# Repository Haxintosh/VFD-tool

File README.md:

# VFD-tool
A modular multitool designed for engineers with a VFD screen (WIP!!!!!!!)

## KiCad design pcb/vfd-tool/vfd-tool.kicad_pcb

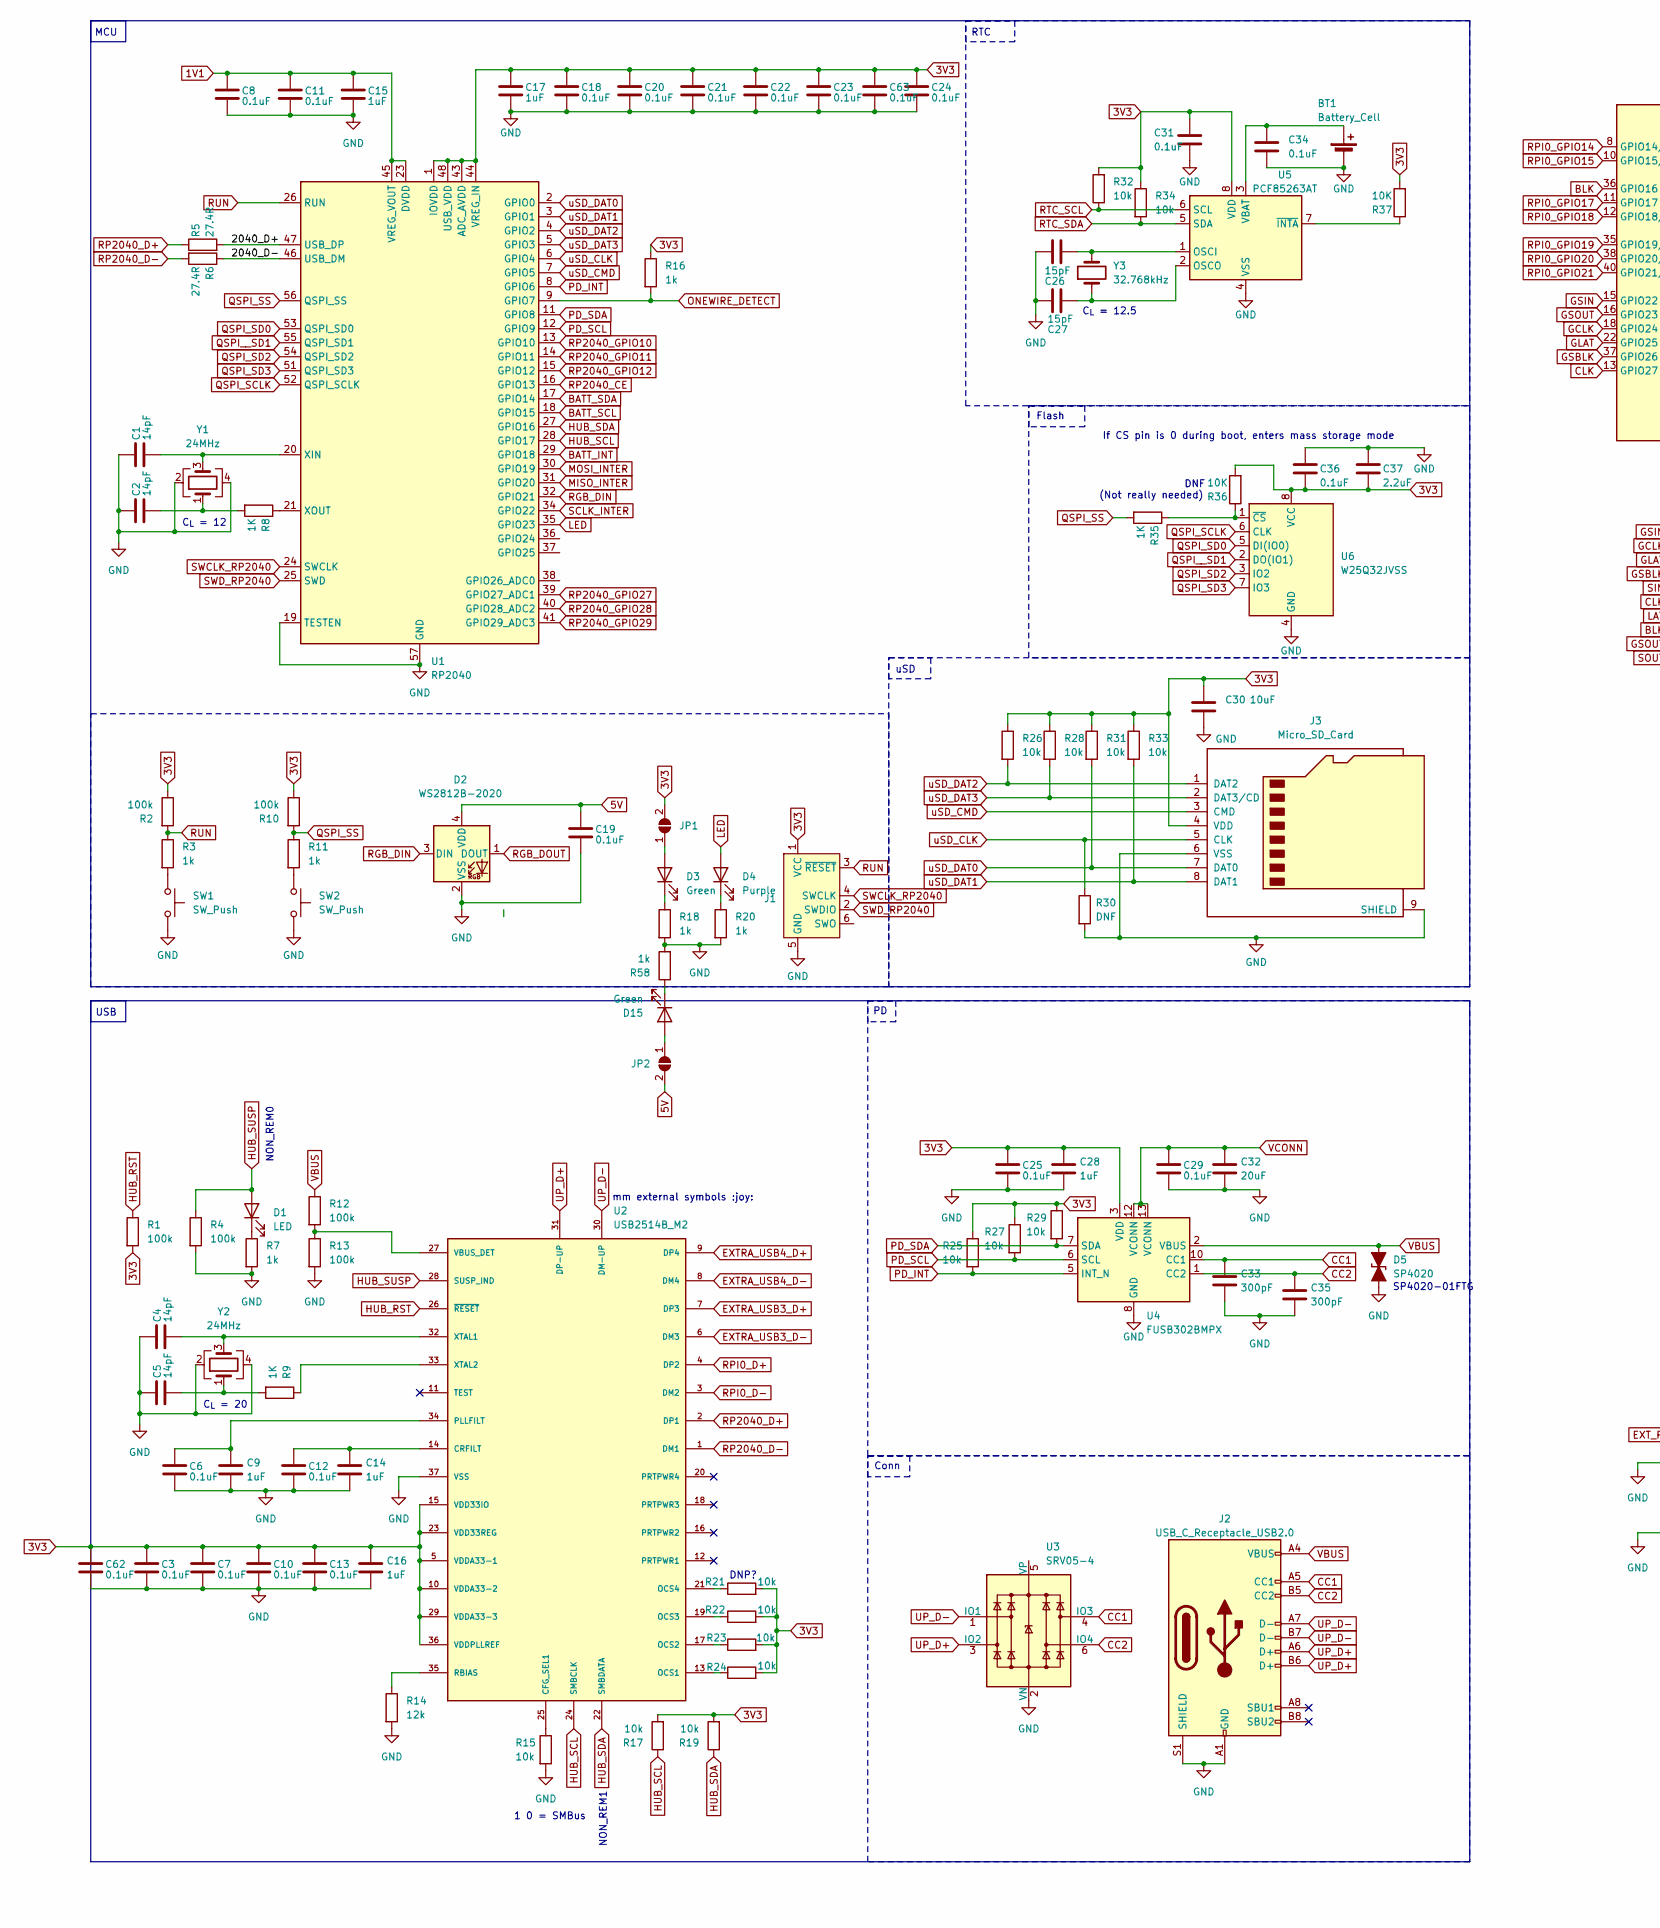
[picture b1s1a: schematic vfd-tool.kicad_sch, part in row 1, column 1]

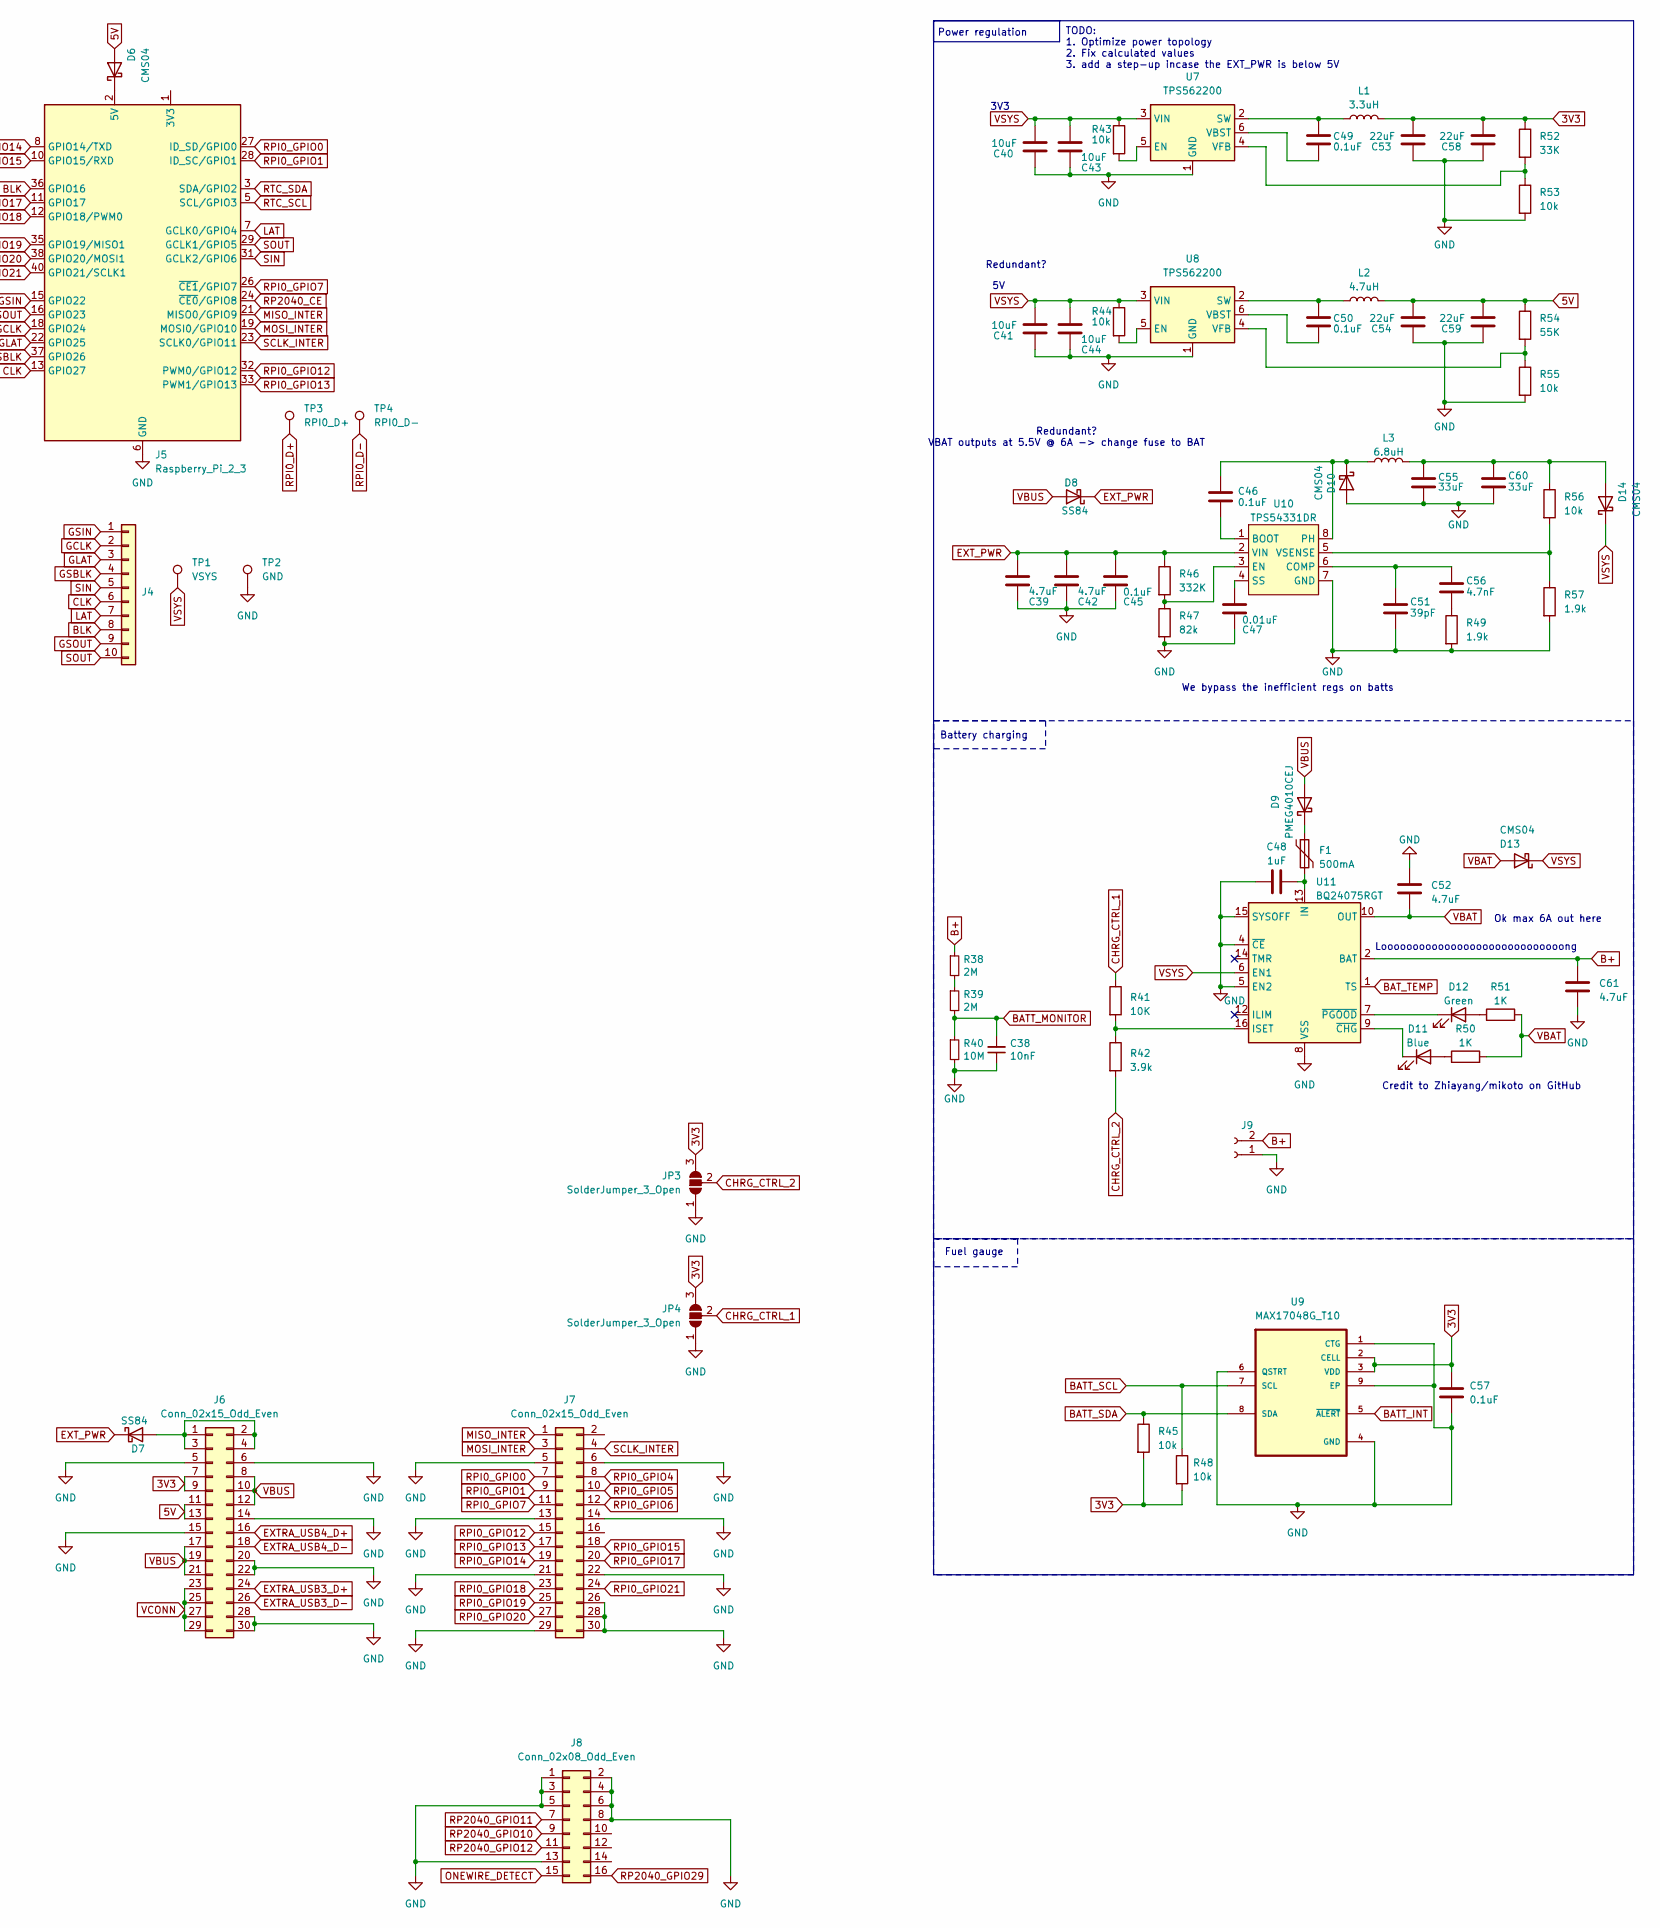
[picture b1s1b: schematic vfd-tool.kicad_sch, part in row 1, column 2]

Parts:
BT1: Battery_Cell; BAT_CR2032-BS-6-1
C1, C2, C4, C5: 14pF; C_0402_1005Metric_Pad0.74x0.62mm_HandSolder
C3, C6, C7, C8, C10, C11, C12, C13, C18, C19, C20, C21, C22, C23, C24, C25, C29, C36, C46, C49, C50, C57, C62, C63: 0.1uF; C_0402_1005Metric_Pad0.74x0.62mm_HandSolder
C9, C14, C15, C17: 1uF; C_0402_1005Metric_Pad0.74x0.62mm_HandSolder
C16: 1uF; R_0402_1005Metric
C26, C27: 15pF; C_0402_1005Metric_Pad0.74x0.62mm_HandSolder
C28: 1uF; C_0603_1608Metric
C30, C40, C41, C43, C44: 10uF; C_0603_1608Metric
C31, C34: 0.1uF; C_0402_1005Metric
C32: 20uF; C_0805_2012Metric
C33, C35: 300pF; C_0402_1005Metric
C37: 2.2uF; C_0603_1608Metric
C38: 10nF; C_0402_1005Metric_Pad0.74x0.62mm_HandSolder; Manufacturer Part CL05B103KB5NNNC; LCSC Part C15195
C39, C42: 4.7uF; C_0805_2012Metric
C45: 0.1uF; C_0603_1608Metric
C47: 0.01uF; C_0402_1005Metric_Pad0.74x0.62mm_HandSolder
C48: 1uF; C_0603_1608Metric_Pad1.08x0.95mm_HandSolder
C51: 39pF; C_0402_1005Metric_Pad0.74x0.62mm_HandSolder
C52, C61: 4.7uF; C_0603_1608Metric_Pad1.08x0.95mm_HandSolder
C53, C54, C58, C59: 22uF; C_0603_1608Metric
C55, C60: 33uF; C_0805_2012Metric
C56: 4.7nF; C_0402_1005Metric_Pad0.74x0.62mm_HandSolder
D1: LED; LED_0603_1608Metric
D2: WS2812B-2020; LED_WS2812B-2020_PLCC4_2.0x2.0mm
D3, D15: Green; LED_0603_1608Metric
D4: Purple; LED_0603_1608Metric
D5: SP4020; D_SOD-323
D6, D10, D13, D14: CMS04; D_SOD-128
D7, D8: SS84; D_SMC
D9: PMEG4010CEJ; D_SOD-323_HandSoldering
D11: Blue; LED_0603_1608Metric_Pad1.05x0.95mm_HandSolder
D12: Green; LED_0603_1608Metric_Pad1.05x0.95mm_HandSolder
F1: 500mA; Fuse_0402_1005Metric_Pad0.77x0.64mm_HandSolder
J1: Conn_ARM_SWD_TagConnect_TC2030-NL; Paw-Connect_RevA_TC2030-IDC-NL_2x03_P1.27mm_Vertical
J2: USB_C_Receptacle_USB2.0; USB_C_Receptacle_G-Switch_GT-USB-7010ASV
J3: Micro_SD_Card; TF-01A
J4: Conn_01x10; MOLEX_5034801000
J5: Raspberry_Pi_2_3; MODULE_ADA3708
J6, J7: Conn_02x15_Odd_Even; PinHeader_2x15_P1.27mm_Vertical
J8: Conn_02x08_Odd_Even; PinHeader_2x08_P1.27mm_Vertical
J9: Conn_01x02_Socket; JST_PH_B2B-PH-SM4-TB_1x02-1MP_P2.00mm_Vertical
JP1, JP2: SolderJumper_2_Open; SolderJumper-2_P1.3mm_Open_TrianglePad1.0x1.5mm
JP3, JP4: SolderJumper_3_Open; SolderJumper-3_P2.0mm_Open_TrianglePad1.0x1.5mm
L1: 3.3uH; L_Chilisin_BMRB00060612
L2: 4.7uH; L_Chilisin_BMRB00060612
L3: 6.8uH; L_Chilisin_BMRB00060612
R1, R2, R4, R10, R12, R13: 100k; R_0402_1005Metric_Pad0.72x0.64mm_HandSolder
R3, R7, R11: 1k; R_0402_1005Metric_Pad0.72x0.64mm_HandSolder
R5, R6: 27.4R; R_0402_1005Metric_Pad0.72x0.64mm_HandSolder
R8, R9, R35, R50, R51: 1K; R_0402_1005Metric_Pad0.72x0.64mm_HandSolder
R14: 12k; R_0402_1005Metric_Pad0.72x0.64mm_HandSolder
R15, R17, R19, R21, R22, R23, R24, R25, R26, R27, R28, R29, R31, R32, R33, R34, R43, R44, R53, R55: 10k; R_0402_1005Metric_Pad0.72x0.64mm_HandSolder
R16, R18, R20, R58: 1k; R_0402_1005Metric
R30: DNF; R_0402_1005Metric_Pad0.72x0.64mm_HandSolder
R36, R37, R41: 10K; R_0402_1005Metric_Pad0.72x0.64mm_HandSolder
R38, R39: 2M; R_0402_1005Metric_Pad0.72x0.64mm_HandSolder; Manufacturer Part RC0402FR-072ML; LCSC Part C138014
R40: 10M; R_0402_1005Metric_Pad0.72x0.64mm_HandSolder; Manufacturer Part RC0402FR-0710ML; LCSC Part C138067
R42: 3.9k; R_0402_1005Metric_Pad0.72x0.64mm_HandSolder
R45, R48: 10k; R_0603_1608Metric
R46: 332K; R_0402_1005Metric
R47: 82k; R_0402_1005Metric
R49, R57: 1.9k; R_0402_1005Metric
R52: 33K; R_0402_1005Metric_Pad0.72x0.64mm_HandSolder
R54: 55K; R_0402_1005Metric_Pad0.72x0.64mm_HandSolder
R56: 10k; R_0402_1005Metric
SW1, SW2: SW_Push; SW_SPST_B3U-1000P
TP1: VSYS; TestPoint_Pad_D3.0mm
TP2: GND; TestPoint_Pad_D3.0mm
TP3: RPI0_D+; TestPoint_Pad_D1.0mm
TP4: RPI0_D-; TestPoint_Pad_D1.0mm
U1: RP2040; QFN-56-1EP_7x7mm_P0.4mm_EP3.2x3.2mm
U2: USB2514B_M2; 36-SQFN-EXPOSED-PAD
U3: SRV05-4; SOT-23-6
U4: FUSB302BMPX; WQFN-14-1EP_2.5x2.5mm_P0.5mm_EP1.45x1.45mm
U5: PCF85263AT; SOIC-8_3.9x4.9mm_P1.27mm
U6: W25Q32JVSS; SOIC-8_5.23x5.23mm_P1.27mm
U7, U8: TPS562200; SOT-23-6
U9: MAX17048G_T10; DFN-8-1EP_2x2mm_P0.5mm_EP0.6x1.2mm
U10: TPS54331DR; SOIC-8_3.9x4.9mm_P1.27mm
U11: BQ24075RGT; VQFN-16-1EP_3x3mm_P0.5mm_EP1.6x1.6mm
Y1, Y2: 24MHz; Crystal_SMD_3225-4Pin_3.2x2.5mm; LCSC C133334
Y3: 32.768kHz; Crystal_SMD_3215-2Pin_3.2x1.5mm

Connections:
1V1: C8.1, C11.1, C15.1, U1.23 (DVDD), U1.45 (VREG_VOUT), U1.50 (DVDD)
3V3: C3.1, C7.1, C10.1, C13.1, C16.1, C17.1, C18.1, C20.1, C21.1, C22.1, C23.1, C24.1, C25.1, C28.1, C30.1, C31.1, C36.2, C37.2, C53.2, C57.1, C58.2, C62.1, C63.1, J1.1 (VCC), J3.4 (VDD), J6.7, J6.9, JP1.2 (B), JP3.3 (B), JP4.3 (B), L1.2, R1.2, R2.1, R10.1, R16.1, R17.2, R19.2, R21.2, R22.2, R23.2, R24.2, R25.1, R26.1, R27.1, R28.1, R29.1, R31.1, R32.2, R33.1, R34.1, R36.2, R37.2, R45.2, R48.2, R52.1, U1.1 (IOVDD), U1.10 (IOVDD), U1.22 (IOVDD), U1.33 (IOVDD), U1.42 (IOVDD), U1.43 (ADC_AVDD), U1.44 (VREG_IN), U1.48 (USB_VDD), U1.49 (IOVDD), U2.5 (VDDA33-1), U2.10 (VDDA33-2), U2.15 (VDD33IO), U2.23 (VDD33REG), U2.29 (VDDA33-3), U2.36 (VDDPLLREF), U4.3 (VDD), U4.4 (VDD), U5.8 (VDD), U6.8 (VCC), U9.2 (CELL), U9.3 (VDD)
5V: C19.1, C54.2, C59.2, D2.4 (VDD), D6.2 (A), J6.11, J6.13, JP2.2 (B), L2.2, R54.1
/2040_D+: R5.2, U1.47 (USB_DP)
/2040_D-: R6.1, U1.46 (USB_DM)
B+: C61.2, J9.2, R38.1, U11.2 (BAT), U11.3 (BAT)
BATT_INT: U1.29 (GPIO18), U9.5 (~ALERT)
BATT_MONITOR: C38.2, R39.2, R40.1
BATT_SCL: R48.1, U1.18 (GPIO15), U9.7 (SCL)
BATT_SDA: R45.1, U1.17 (GPIO14), U9.8 (SDA)
BAT_TEMP: U11.1 (TS)
BLK: J4.8, J5.36 (GPIO16)
CC1: C33.1, J2.A5 (CC1), U3.4 (IO3), U4.10 (CC1), U4.11 (CC1)
CC2: C35.1, J2.B5 (CC2), U3.6 (IO4), U4.1 (CC2), U4.14 (CC2)
CHRG_CTRL_1: JP4.2 (C), R41.1
CHRG_CTRL_2: JP3.2 (C), R42.2
CLK: J4.6, J5.13 (GPIO27)
EXTRA_USB3_D+: J6.24, U2.7 (DP3)
EXTRA_USB3_D-: J6.26, U2.6 (DM3)
EXTRA_USB4_D+: J6.16, U2.9 (DP4)
EXTRA_USB4_D-: J6.18, U2.8 (DM4)
EXT_PWR: C39.1, C42.1, C45.1, D7.1 (K), D8.1 (K), R46.1, U10.2 (VIN)
GCLK: J4.2, J5.18 (GPIO24)
GLAT: J4.3, J5.22 (GPIO25)
GND: BT1.N (-), C1.1, C2.1, C3.2, C4.1, C5.1, C6.2, C7.2, C8.2, C9.2, C10.2, C11.2, C12.2, C13.2, C14.2, C15.2, C16.2, C17.2, C18.2, C19.2, C20.2, C21.2, C22.2, C23.2, C24.2, C25.2, C26.2, C27.2, C28.2, C29.2, C30.2, C31.2, C32.2, C33.2, C34.2, C35.2, C36.1, C37.1, C38.1, C39.2, C40.1, C41.1, C42.2, C43.2, C44.2, C45.2, C47.2, C48.2, C51.2, C52.1, C53.1, C54.1, C55.2, C57.2, C58.1, C59.1, C60.2, C61.1, C62.2, C63.2, D2.2 (VSS), D5.2 (A2), D10.2 (A), J1.5 (GND), J2.A1 (GND), J2.A12 (GND), J2.B1 (GND), J2.B12 (GND), J2.S1 (SHIELD), J3.6 (VSS), J3.9 (SHIELD), J5.6 (GND), J5.9 (GND), J5.14 (GND), J5.20 (GND), J5.25 (GND), J5.30 (GND), J5.34 (GND), J5.39 (GND), J6.5, J6.6, J6.14, J6.15, J6.20, J6.22, J6.28, J6.30, J7.5, J7.6, J7.13, J7.14, J7.21, J7.22, J7.26, J7.28, J7.29, J7.30, J8.1, J8.2, J8.3, J8.4, J8.5, J8.6, J8.8, J8.13, J9.1, JP3.1 (A), JP4.1 (A), R4.2, R7.2, R13.2, R14.2, R15.2, R18.2, R20.2, R30.2, R40.2, R47.2, R49.2, R53.2, R55.2, R57.2, R58.2, SW1.2, SW2.2, TP2.1, U1.19 (TESTEN), U1.57 (GND), U2.37 (VSS), U3.2 (VN), U4.8 (GND), U4.9 (GND), U4.15 (GND), U5.4 (VSS), U6.4 (GND), U7.1 (GND), U8.1 (GND), U9.1 (CTG), U9.4 (GND), U9.6 (QSTRT), U9.9 (EP), U10.7 (GND), U11.4 (~CE), U11.5 (EN2), U11.8 (VSS), U11.15 (SYSOFF), U11.17 (VSS), Y1.2, Y1.4, Y2.2, Y2.4
GSBLK: J4.4, J5.37 (GPIO26)
GSIN: J4.1, J5.15 (GPIO22)
GSOUT: J4.9, J5.16 (GPIO23)
HUB_RST: R1.1, U2.26 (~RESET)
HUB_SCL: R17.1, U1.28 (GPIO17), U2.24 (SMBCLK)
HUB_SDA: R19.1, U1.27 (GPIO16), U2.22 (SMBDATA)
HUB_SUSP: D1.2 (A), R4.1, U2.28 (SUSP_IND)
LAT: J4.7, J5.7 (GCLK0/GPIO4)
LED: D4.2 (A), U1.35 (GPIO23)
MISO_INTER: J5.21 (MISO0/GPIO9), J7.1, U1.31 (GPIO20)
MOSI_INTER: J5.19 (MOSI0/GPIO10), J7.3, U1.30 (GPIO19)
unnamed: BT1.P (+), C34.1, U5.3 (VBAT)
unnamed: C2.2, R8.2, Y1.1
unnamed: C5.2, R9.2, Y2.1
unnamed: C56.2, R49.1
unnamed: D1.1 (K), R7.1
unnamed: D3.2 (A), JP1.1 (A)
unnamed: D3.1 (K), R18.1
unnamed: D4.1 (K), R20.1
unnamed: D6.1 (K), J5.2 (5V), J5.4 (5V)
unnamed: D7.2 (A), J6.1, J6.2, J6.3, J6.4
unnamed: D9.1 (K), F1.1
unnamed: C46.1, D10.1 (K), L3.1, U10.8 (PH)
unnamed: D11.2 (A), R50.1
unnamed: D11.1 (K), U11.9 (~CHG)
unnamed: D12.2 (A), R51.1
unnamed: D12.1 (K), U11.7 (~PGOOD)
unnamed: C55.1, C60.1, D14.2 (A), L3.2, R56.1
unnamed: D15.2 (A), JP2.1 (A)
unnamed: D15.1 (K), R58.1
unnamed: J5.1 (3V3), J5.17 (3V3)
unnamed: R3.2, SW1.1
unnamed: R11.2, SW2.1
unnamed: R38.2, R39.1
unnamed: C1.2, U1.20 (XIN), Y1.3
unnamed: R8.1, U1.21 (XOUT)
unnamed: R15.1, U2.25 (CFG_SEL1)
unnamed: C12.1, C14.1, U2.14 (CRFILT)
unnamed: R24.1, U2.13 (OCS1)
unnamed: R23.1, U2.17 (OCS2)
unnamed: R22.1, U2.19 (OCS3)
unnamed: R21.1, U2.21 (OCS4)
unnamed: C6.1, C9.1, U2.34 (PLLFILT)
unnamed: R14.1, U2.35 (RBIAS)
unnamed: R12.2, R13.1, U2.27 (VBUS_DET)
unnamed: C4.2, U2.32 (XTAL1), Y2.3
unnamed: R9.1, U2.33 (XTAL2)
unnamed: C26.1, U5.1 (OSCI), Y3.2
unnamed: C27.1, U5.2 (OSCO), Y3.1
unnamed: R37.1, U5.7 (~INTA)
unnamed: R35.1, R36.1, U6.1 (~CS)
unnamed: R43.2, U7.5 (EN)
unnamed: C49.1, L1.1, U7.2 (SW)
unnamed: C49.2, U7.6 (VBST)
unnamed: R52.2, R53.1, U7.4 (VFB)
unnamed: R44.2, U8.5 (EN)
unnamed: C50.1, L2.1, U8.2 (SW)
unnamed: C50.2, U8.6 (VBST)
unnamed: R54.2, R55.1, U8.4 (VFB)
unnamed: C46.2, U10.1 (BOOT)
unnamed: C51.1, C56.1, U10.6 (COMP)
unnamed: R46.2, R47.1, U10.3 (EN)
unnamed: C47.1, U10.4 (SS)
unnamed: R56.2, R57.1, U10.5 (VSENSE)
unnamed: C48.1, F1.2, U11.13 (IN)
unnamed: R41.2, R42.1, U11.16 (ISET)
ONEWIRE_DETECT: J8.15, R16.2, U1.9 (GPIO7)
PD_INT: R25.2, U1.8 (GPIO6), U4.5 (INT_N)
PD_SCL: R27.2, U1.12 (GPIO9), U4.6 (SCL)
PD_SDA: R29.2, U1.11 (GPIO8), U4.7 (SDA)
QSPI_SCLK: U1.52 (QSPI_SCLK), U6.6 (CLK)
QSPI_SD0: U1.53 (QSPI_SD0), U6.5 (DI(IO0))
QSPI_SD2: U1.54 (QSPI_SD2), U6.3 (IO2)
QSPI_SD3: U1.51 (QSPI_SD3), U6.7 (IO3)
QSPI_SS: R10.2, R11.1, R35.2, U1.56 (QSPI_SS)
QSPI__SD1: U1.55 (QSPI_SD1), U6.2 (DO(IO1))
RGB_DIN: D2.3 (DIN), U1.32 (GPIO21)
RGB_DOUT: D2.1 (DOUT)
RP2040_CE: J5.24 (~CE0/GPIO8), U1.16 (GPIO13)
RP2040_D+: R5.1, U2.2 (DP1)
RP2040_D-: R6.2, U2.1 (DM1)
RP2040_GPIO10: J8.9, U1.13 (GPIO10)
RP2040_GPIO11: J8.7, U1.14 (GPIO11)
RP2040_GPIO12: J8.11, U1.15 (GPIO12)
RP2040_GPIO27: U1.39 (GPIO27_ADC1)
RP2040_GPIO28: U1.40 (GPIO28_ADC2)
RP2040_GPIO29: J8.16, U1.41 (GPIO29_ADC3)
RPI0_D+: TP3.1, U2.4 (DP2)
RPI0_D-: TP4.1, U2.3 (DM2)
RPI0_GPIO0: J5.27 (ID_SD/GPIO0), J7.7
RPI0_GPIO1: J5.28 (ID_SC/GPIO1), J7.9
RPI0_GPIO4: J7.8
RPI0_GPIO5: J7.10
RPI0_GPIO6: J7.12
RPI0_GPIO7: J5.26 (~CE1/GPIO7), J7.11
RPI0_GPIO12: J5.32 (PWM0/GPIO12), J7.15
RPI0_GPIO13: J5.33 (PWM1/GPIO13), J7.17
RPI0_GPIO14: J5.8 (GPIO14/TXD), J7.19
RPI0_GPIO15: J5.10 (GPIO15/RXD), J7.18
RPI0_GPIO17: J5.11 (GPIO17), J7.20
RPI0_GPIO18: J5.12 (GPIO18/PWM0), J7.23
RPI0_GPIO19: J5.35 (GPIO19/MISO1), J7.25
RPI0_GPIO20: J5.38 (GPIO20/MOSI1), J7.27
RPI0_GPIO21: J5.40 (GPIO21/SCLK1), J7.24
RTC_SCL: J5.5 (SCL/GPIO3), R32.1, U5.6 (SCL)
RTC_SDA: J5.3 (SDA/GPIO2), R34.2, U5.5 (SDA)
RUN: J1.3 (~RESET), R2.2, R3.1, U1.26 (RUN)
SCLK_INTER: J5.23 (SCLK0/GPIO11), J7.4, U1.34 (GPIO22)
SIN: J4.5, J5.31 (GCLK2/GPIO6)
SOUT: J4.10, J5.29 (GCLK1/GPIO5)
SWCLK_RP2040: J1.4 (SWCLK), U1.24 (SWCLK)
SWD_RP2040: J1.2 (SWDIO), U1.25 (SWD)
UP_D+: J2.A6 (D+), J2.B6 (D+), U2.31 (DP-UP), U3.3 (IO2)
UP_D-: J2.A7 (D-), J2.B7 (D-), U2.30 (DM-UP), U3.1 (IO1)
VBAT: C52.2, D13.2 (A), R50.2, R51.2, U11.10 (OUT), U11.11 (OUT)
VBUS: D5.1 (A1), D8.2 (A), D9.2 (A), J2.A4 (VBUS), J2.A9 (VBUS), J2.B4 (VBUS), J2.B9 (VBUS), J6.8, J6.10, J6.12, J6.17, J6.19, J6.21, R12.1, U4.2 (VBUS)
VCONN: C29.1, C32.1, J6.23, J6.25, J6.27, J6.29, U4.12 (VCONN), U4.13 (VCONN)
VSYS: C40.2, C41.2, C43.1, C44.1, D13.1 (K), D14.1 (K), R43.1, R44.1, TP1.1, U7.3 (VIN), U8.3 (VIN), U11.6 (EN1)
uSD_CLK: J3.5 (CLK), R30.1, U1.6 (GPIO4)
uSD_CMD: J3.3 (CMD), U1.7 (GPIO5)
uSD_DAT0: J3.7 (DAT0), R31.2, U1.2 (GPIO0)
uSD_DAT1: J3.8 (DAT1), R33.2, U1.3 (GPIO1)
uSD_DAT2: J3.1 (DAT2), R26.2, U1.4 (GPIO2)
uSD_DAT3: J3.2 (DAT3/CD), R28.2, U1.5 (GPIO3)

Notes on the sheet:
Credit to Zhiayang/mikoto on GitHub
Fuel gauge
3V3
Battery charging
Conn
NON_REM1
Flash
C_{L} = 12.5
MCU
C_{L} = 12
Looooooooooooooooooooooooooooong
Redundant?
DNF (Not really needed)
We bypass the inefficient regs on batts
mm external symbols :joy:
C_{L} = 20
Power regulation
uSD
If CS pin is 0 during boot, enters mass storage mode
Redundant? VBAT outputs at 5.5V @ 6A -> change fuse to BAT
NON_REM0
RTC
DNP?
1 0 = SMBus
Ok max 6A out here
USB
SP4020-01FTG
TODO: 1. Optimize power topology 2. Fix calculated values 3. add a step-up incase the EXT_PWR is below 5V

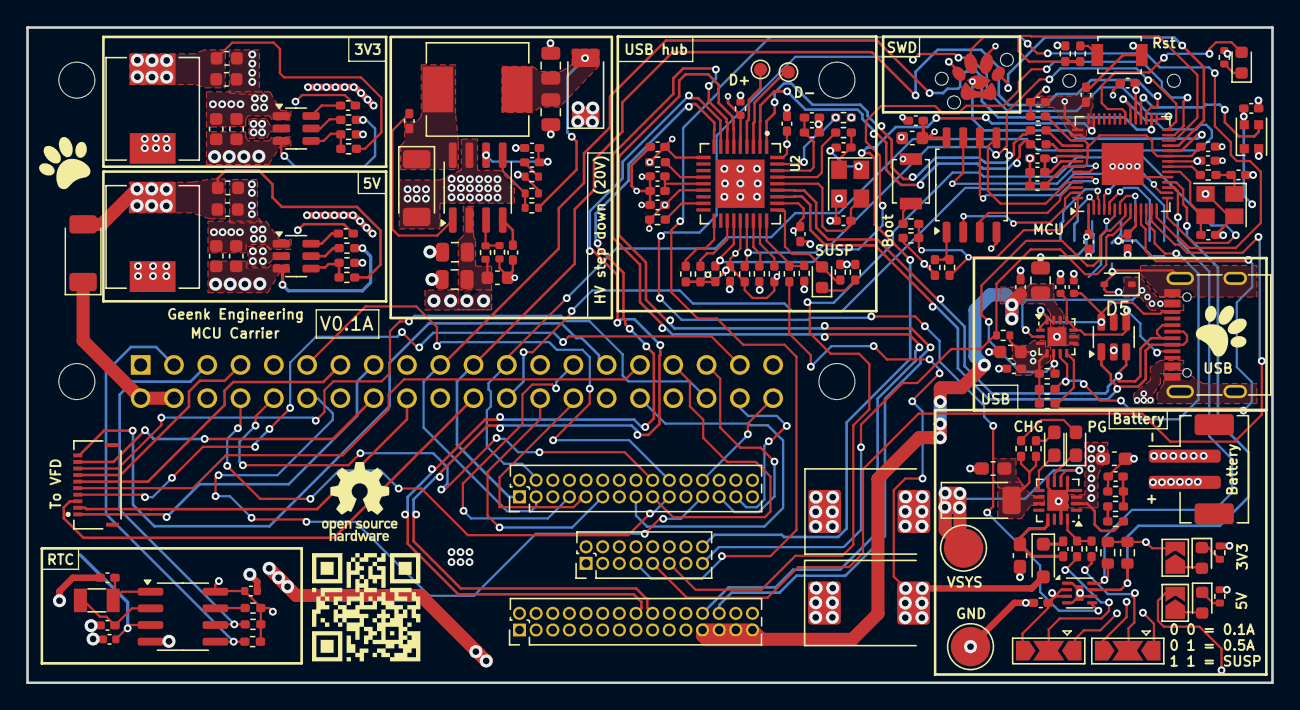
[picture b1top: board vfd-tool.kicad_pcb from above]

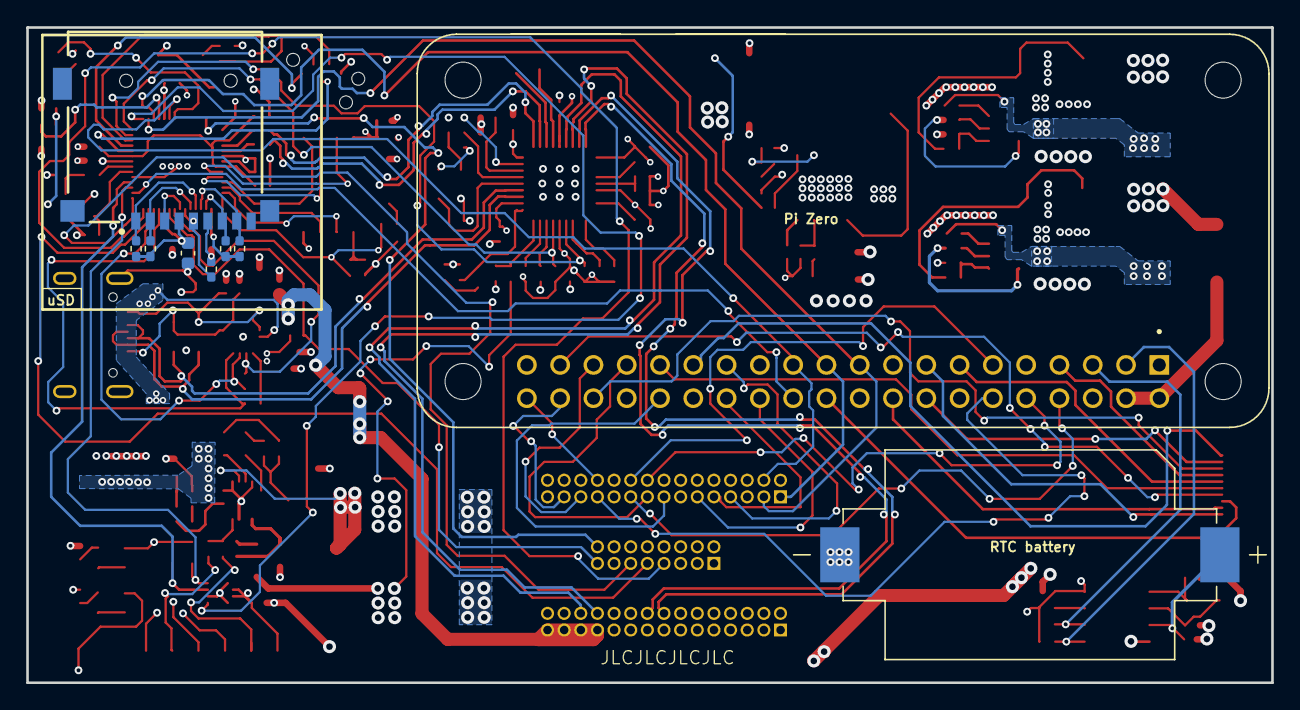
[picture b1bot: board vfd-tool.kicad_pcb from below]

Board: 4 copper layers, 95.0 x 50.0 mm, 176 parts (9 on the bottom side), 142 nets.

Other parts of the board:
G**: Paw-Connect_Silk_Full
G**#2: Paw-Connect_Silk_Full

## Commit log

2024-06-18 MCU part of the schematic done (ish...)
2024-06-20 Charging circuitry kinda done
2024-06-22 USB hub WIP
2024-06-23 USB hub & PD done
2024-06-23 Added switching regulator for VBUS (+20V), Board to board connector
2024-06-24 added RTC
2024-06-27 assigned footprints to most of the passives
2024-06-28 recalculated values for the regulators and found LCSC components for most of the symbols
2024-06-29 Fixed footprints
2024-06-30 USB + PD sections kinda done, started on battery charging
2024-07-01 3V3 + Charging + Fuel gauge PCB done
2024-07-01 5V & USB hub done
2024-07-02 Flash done and the majority of the RP2040 mcu done
2024-07-02 5V power done and general layour of of the PCB
2024-07-03 finished interconnect, started on internal power layer
2024-07-03 Power plane kinda done
2024-07-03 DRC Fixed and added solder jumpers
2024-07-04 3D fixed + silkscreen
2024-07-04 pre-final commit
2024-08-27 fix #1 and #2
2024-08-27 pcb fix for #1 and #2
